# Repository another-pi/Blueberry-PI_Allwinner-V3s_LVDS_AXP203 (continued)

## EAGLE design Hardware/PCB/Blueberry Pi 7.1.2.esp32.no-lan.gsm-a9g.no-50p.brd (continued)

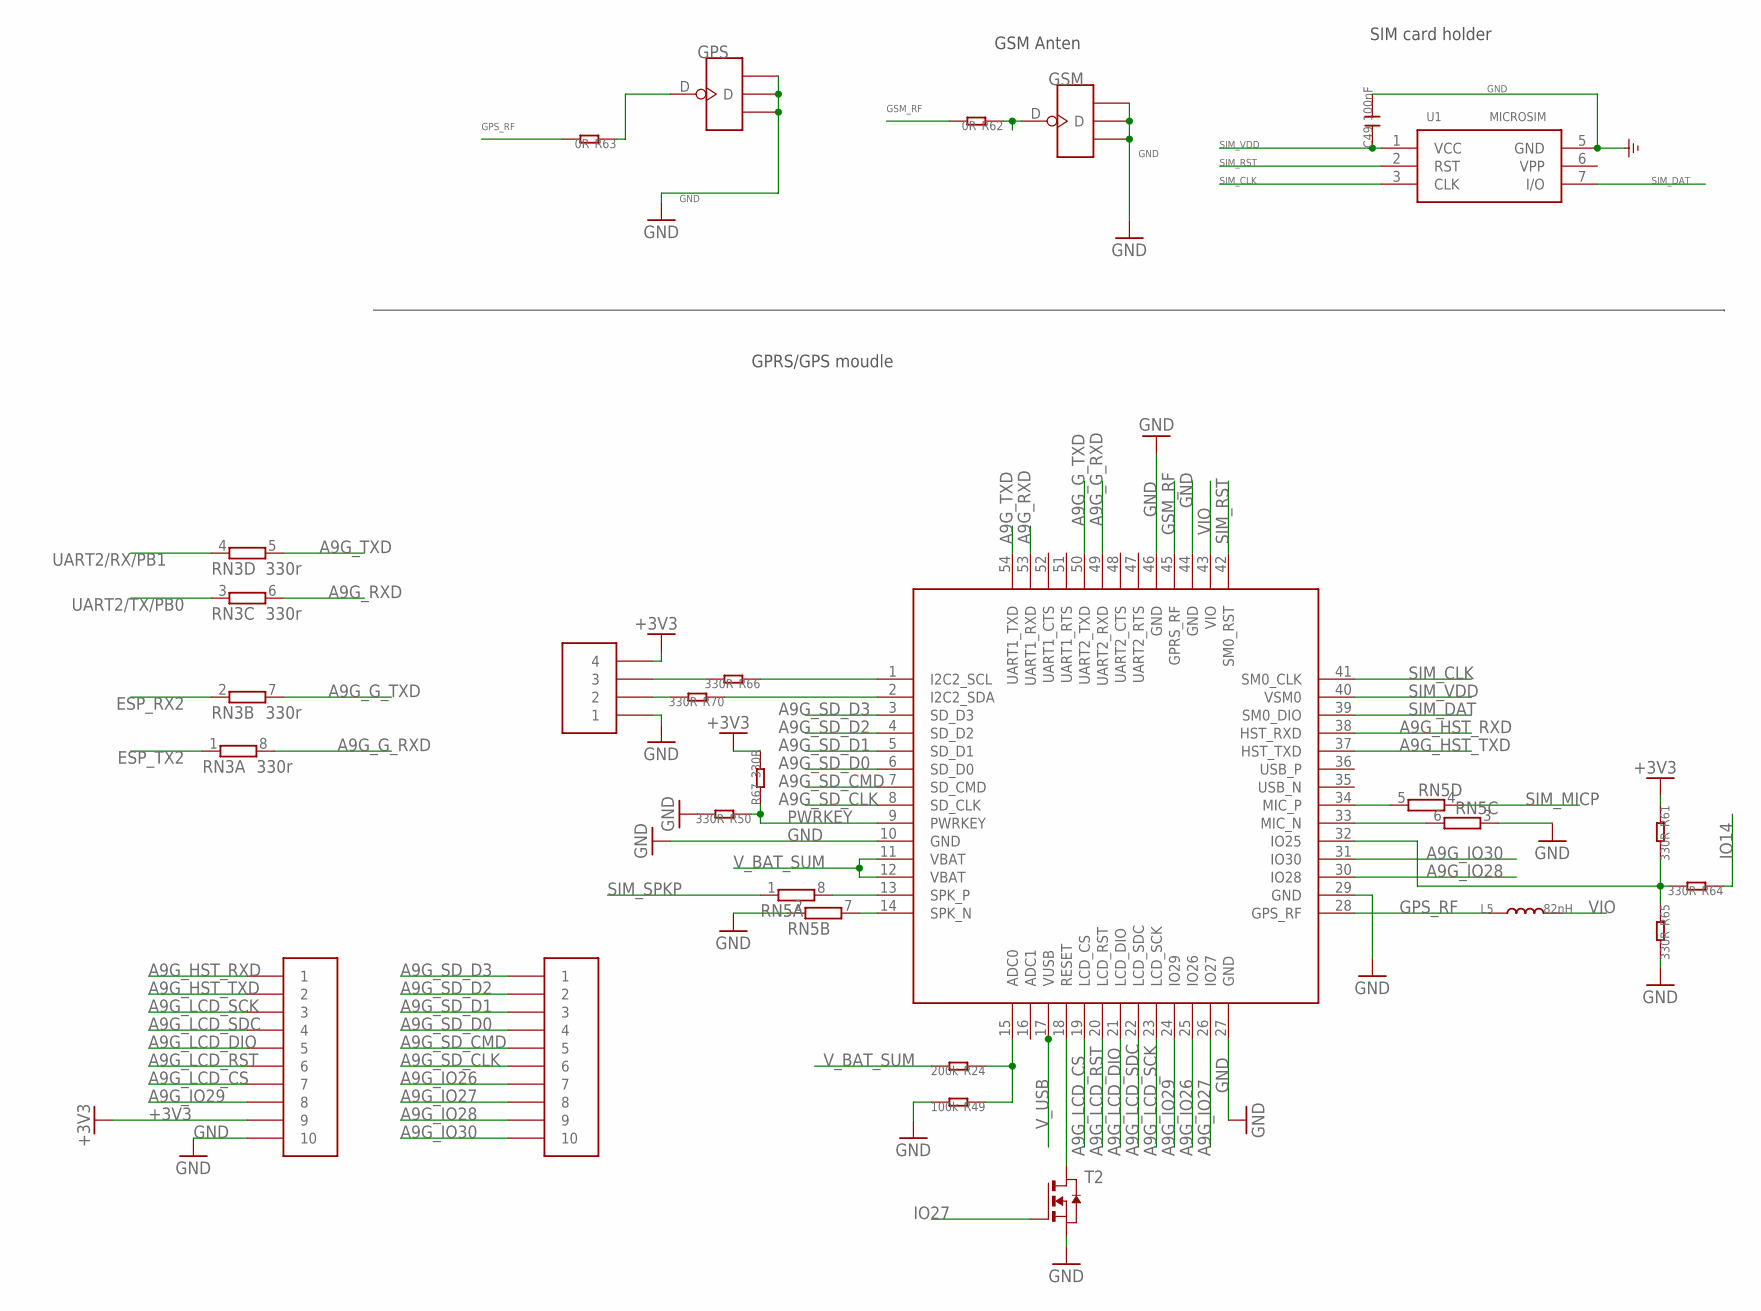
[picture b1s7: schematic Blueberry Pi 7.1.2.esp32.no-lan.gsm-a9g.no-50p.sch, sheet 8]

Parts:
C49: 100nF; C0603
DBG-COM1, DBG-COM2: HDR-1.27MM-110; HDR-1.27MM-1*10
GPS: ANTENNA-U-FL; 4P-U-FL
GSM: ANTENNA-U-FL; 4P-U-FL
L5: 82nH; L0603
R24: 200k; R0603
R49: 100k; R0603
R50, R61, R64, R65, R66, R67, R70: 330R; R0603
R62, R63: 0R; R0603
RN3: 330r; EXB38V
RN5: 4R-NEXB38V; EXB38V
T2: NMOSSOT23; SOT-23
U1: MICROSIM
U6: A9G
U$20: HDR-1.27MM-14; HDR-1.27MM-1*4

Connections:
+3V3: DBG-COM1.P$9 (9), R61.1, R67.2, U$20.P$4 (4); also elsewhere on the board
A9G_G_RXD: RN3.8 (2), U6.49 (UART2_RXD)
A9G_G_TXD: RN3.7 (2), U6.50 (UART2_TXD)
A9G_HST_RXD: DBG-COM1.P$1 (1), U6.38 (HST_RXD)
A9G_HST_TXD: DBG-COM1.P$2 (2), U6.37 (HST_TXD)
A9G_IO26: DBG-COM2.P$7 (7), U6.25 (IO26)
A9G_IO27: DBG-COM2.P$8 (8), U6.26 (IO27)
A9G_IO28: DBG-COM2.P$9 (9), U6.30 (IO28)
A9G_IO29: DBG-COM1.P$8 (8), U6.24 (IO29)
A9G_IO30: DBG-COM2.P$10 (10), U6.31 (IO30)
A9G_LCD_CS: DBG-COM1.P$7 (7), U6.19 (LCD_CS)
A9G_LCD_DIO: DBG-COM1.P$5 (5), U6.21 (LCD_DIO)
A9G_LCD_RST: DBG-COM1.P$6 (6), U6.20 (LCD_RST)
A9G_LCD_SCK: DBG-COM1.P$3 (3), U6.23 (LCD_SCK)
A9G_LCD_SDC: DBG-COM1.P$4 (4), U6.22 (LCD_SDC)
A9G_RXD: RN3.6 (2), U6.53 (UART1_RXD)
A9G_SD_CLK: DBG-COM2.P$6 (6), U6.8 (SD_CLK)
A9G_SD_CMD: DBG-COM2.P$5 (5), U6.7 (SD_CMD)
A9G_SD_D0: DBG-COM2.P$4 (4), U6.6 (SD_D0)
A9G_SD_D1: DBG-COM2.P$3 (3), U6.5 (SD_D1)
A9G_SD_D2: DBG-COM2.P$2 (2), U6.4 (SD_D2)
A9G_SD_D3: DBG-COM2.P$1 (1), U6.3 (SD_D3)
A9G_TXD: RN3.5 (2), U6.54 (UART1_TXD)
ESP_RX2: RN3.2 (1); also elsewhere on the board
ESP_TX2: RN3.1; also elsewhere on the board
GND: C49.2, DBG-COM1.P$10 (10), GPS.GND1, GPS.GND2, GPS.GND3, GSM.GND1, GSM.GND2, GSM.GND3, R49.2, R50.2, R65.2, RN5.2 (1), RN5.3 (1), T2.2 (S), U1.5 (GND), U6.10 (GND), U6.27 (GND), U6.29 (GND), U6.44 (GND), U6.46 (GND), U$20.P$1 (1); also elsewhere on the board
GPS_RF: L5.1, R63.2, U6.28 (GPS_RF)
GSM_RF: R62.2, U6.45 (GPRS_RF)
IO14: R64.1; also elsewhere on the board
IO27: T2.3 (G); also elsewhere on the board
unnamed: R24.1, R49.1, U6.15 (ADC0)
unnamed: RN5.6 (2), U6.33 (MIC_N)
unnamed: RN5.7 (2), U6.14 (SPK_N)
unnamed: R61.2, R64.2, R65.1, U6.32 (IO25)
unnamed: T2.1 (D), U6.18 (RESET)
unnamed: RN5.8 (2), U6.13 (SPK_P)
unnamed: R66.1, U6.1 (I2C2_SCL)
unnamed: GSM.D, R62.1
unnamed: GPS.D, R63.1
unnamed: R70.2, U$20.P$2 (2)
unnamed: R70.1, U6.2 (I2C2_SDA)
unnamed: RN5.5 (2), U6.34 (MIC_P)
unnamed: R66.2, U$20.P$3 (3)
PWRKEY: R50.1, R67.1, U6.9 (PWRKEY)
SIM_CLK: U1.3 (CLK), U6.41 (SM0_CLK)
SIM_DAT: U1.7 (I/O), U6.39 (SM0_DIO)
SIM_MICP: RN5.4 (1); also elsewhere on the board
SIM_RST: U1.2 (RST), U6.42 (SM0_RST)
SIM_SPKP: RN5.1; also elsewhere on the board
SIM_VDD: C49.1, U1.1 (VCC), U6.40 (VSM0)
UART2/RX/PB1: RN3.4 (1); also elsewhere on the board
UART2/TX/PB0: RN3.3 (1); also elsewhere on the board
VIO: L5.2, U6.43 (VIO)
V_BAT_SUM: R24.2, U6.11 (VBAT), U6.12 (VBAT); also elsewhere on the board
V_USB: U6.17 (VUSB); also elsewhere on the board

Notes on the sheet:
SIM card holder
GSM Anten
GPRS/GPS moudle

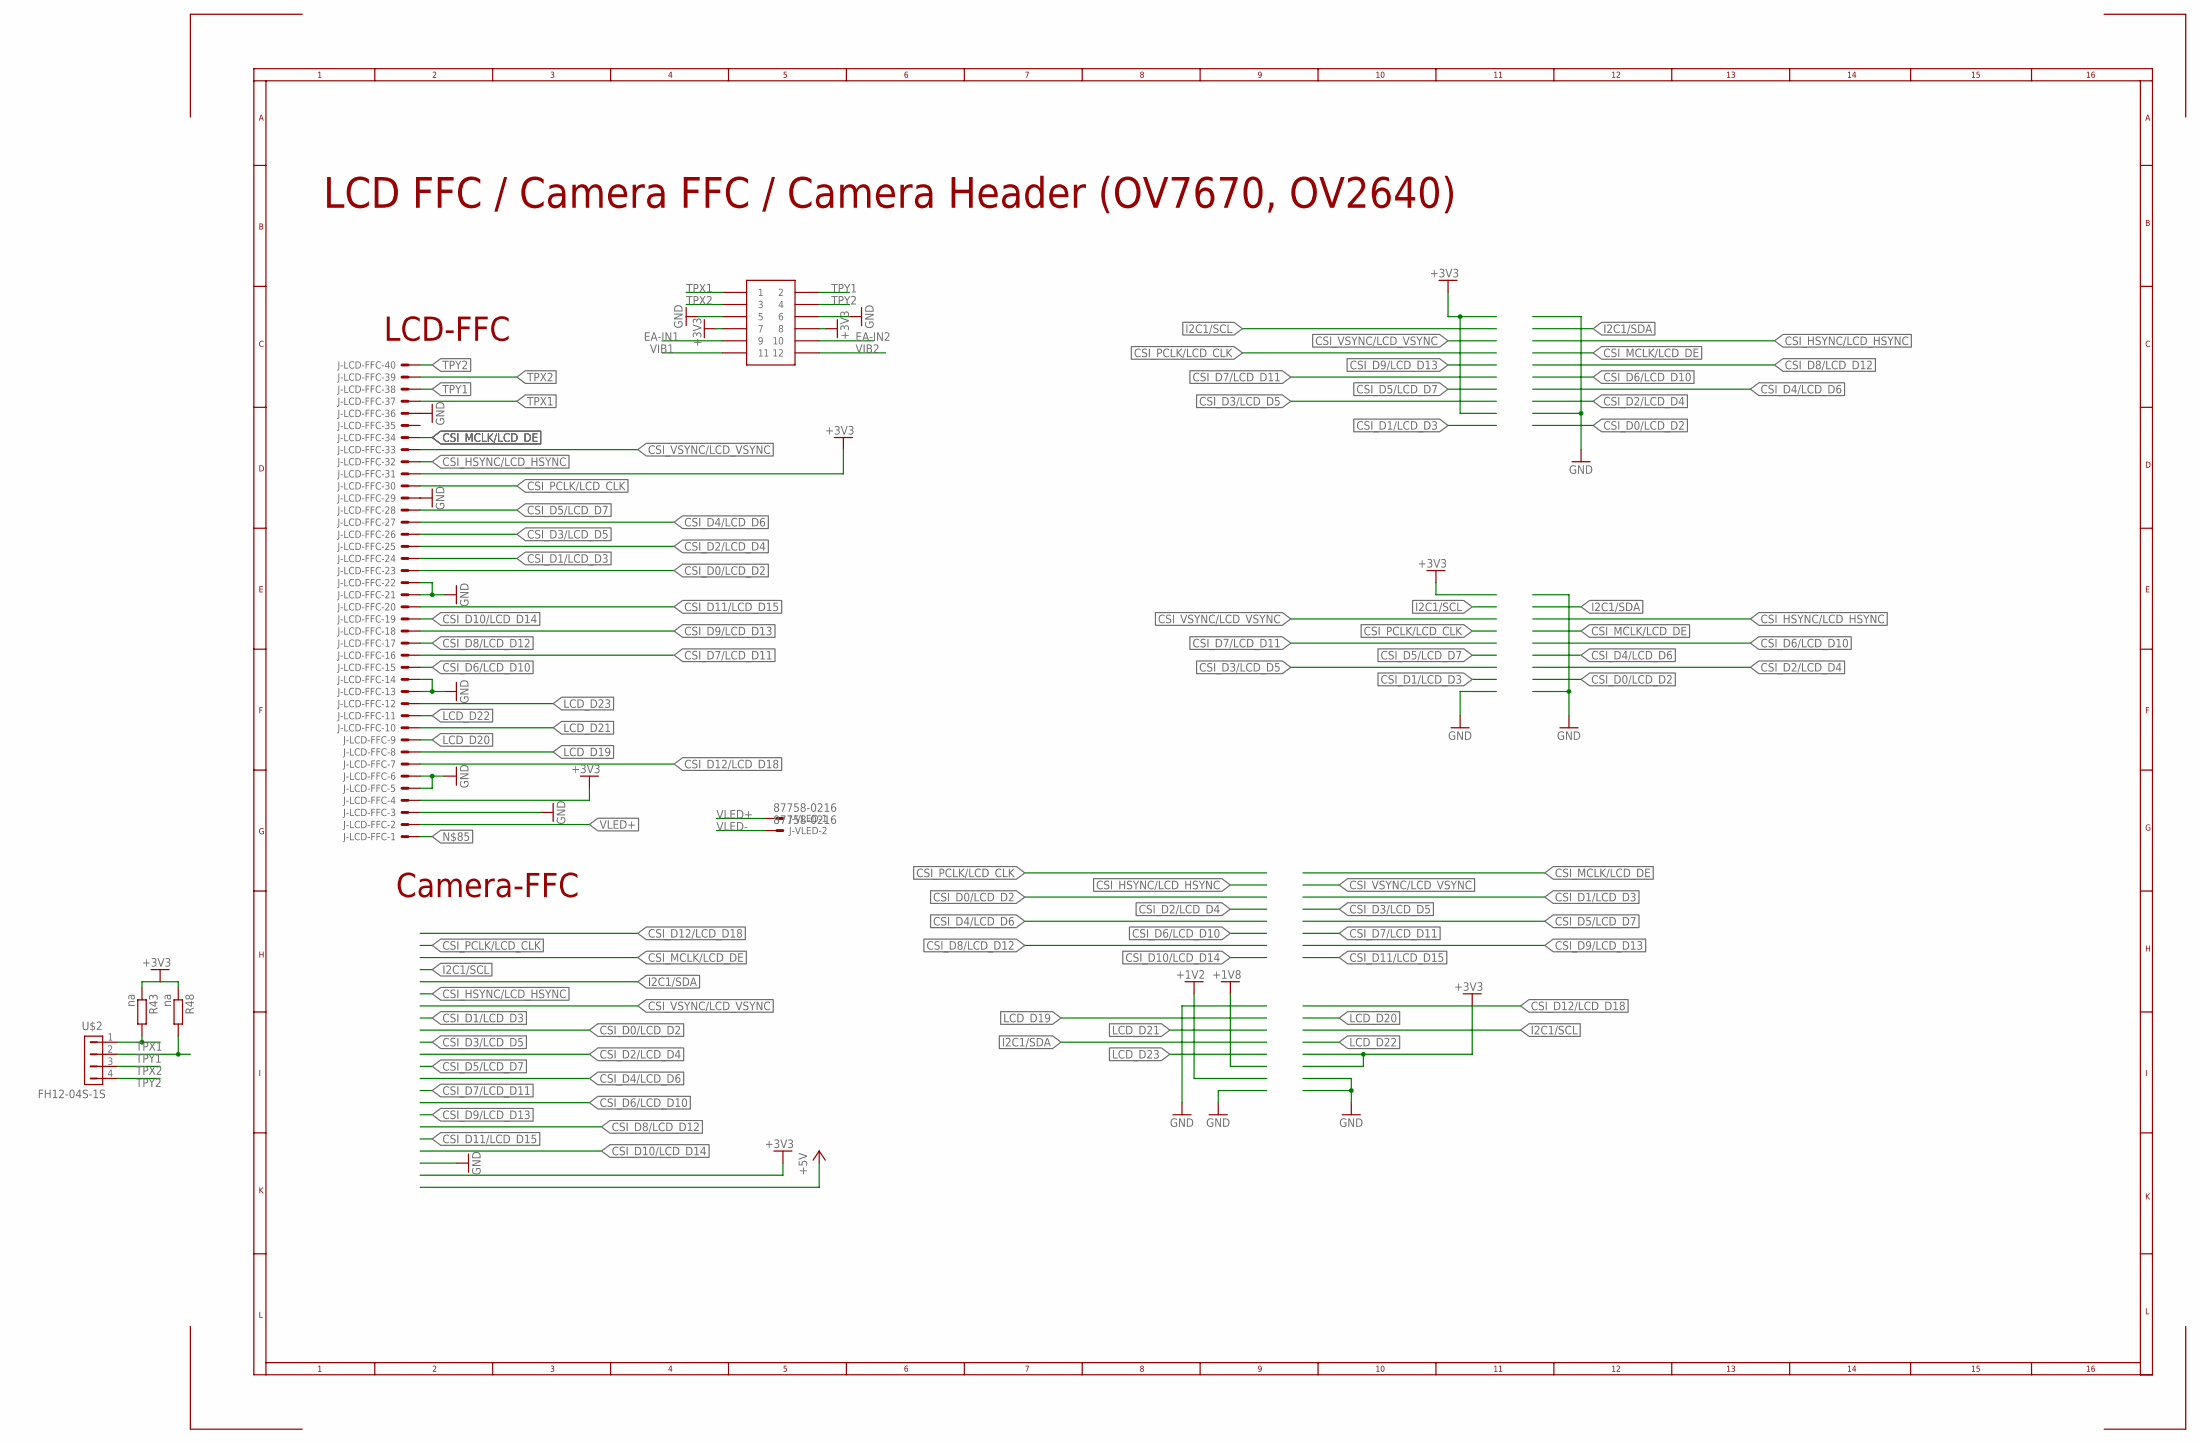
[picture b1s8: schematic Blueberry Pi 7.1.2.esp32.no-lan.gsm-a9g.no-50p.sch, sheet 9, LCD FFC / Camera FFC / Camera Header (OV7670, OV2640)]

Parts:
J-LCD-FFC: 40PINFPCH15-1LW; XF2H-4015-1LW
J-VLED: 87758-0216
R43, R48: na; R0603
U$2: FH12-04S-1S; FH12-04S-1SH
U$18: HDR-1.27MM-62; HDR-1.27MM-6*2

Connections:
+3V3: J-LCD-FFC.4 (MS), J-LCD-FFC.31 (MS), R43.1, R48.1, U$18.P$7 (7), U$18.P$8 (8); also elsewhere on the board
CSI_D0/LCD_D2: J-LCD-FFC.23 (MS); also elsewhere on the board
CSI_D1/LCD_D3: J-LCD-FFC.24 (MS); also elsewhere on the board
CSI_D2/LCD_D4: J-LCD-FFC.25 (MS); also elsewhere on the board
CSI_D3/LCD_D5: J-LCD-FFC.26 (MS); also elsewhere on the board
CSI_D4/LCD_D6: J-LCD-FFC.27 (MS); also elsewhere on the board
CSI_D5/LCD_D7: J-LCD-FFC.28 (MS); also elsewhere on the board
CSI_D6/LCD_D10: J-LCD-FFC.15 (MS); also elsewhere on the board
CSI_D7/LCD_D11: J-LCD-FFC.16 (MS); also elsewhere on the board
CSI_D8/LCD_D12: J-LCD-FFC.17 (MS); also elsewhere on the board
CSI_D9/LCD_D13: J-LCD-FFC.18 (MS); also elsewhere on the board
CSI_D10/LCD_D14: J-LCD-FFC.19 (MS); also elsewhere on the board
CSI_D11/LCD_D15: J-LCD-FFC.20 (MS); also elsewhere on the board
CSI_D12/LCD_D18: J-LCD-FFC.7 (MS); also elsewhere on the board
CSI_HSYNC/LCD_HSYNC: J-LCD-FFC.32 (MS); also elsewhere on the board
CSI_MCLK/LCD_DE: J-LCD-FFC.34 (MS); also elsewhere on the board
CSI_PCLK/LCD_CLK: J-LCD-FFC.30 (MS); also elsewhere on the board
CSI_VSYNC/LCD_VSYNC: J-LCD-FFC.33 (MS); also elsewhere on the board
EA-IN1: U$18.P$9 (9); also elsewhere on the board
EA-IN2: U$18.P$10 (10); also elsewhere on the board
GND: J-LCD-FFC.3 (MS), J-LCD-FFC.5 (MS), J-LCD-FFC.6 (MS), J-LCD-FFC.13 (MS), J-LCD-FFC.14 (MS), J-LCD-FFC.21 (MS), J-LCD-FFC.22 (MS), J-LCD-FFC.29 (MS), J-LCD-FFC.36 (MS), U$18.P$5 (5), U$18.P$6 (6); also elsewhere on the board
LCD_D19: J-LCD-FFC.8 (MS); also elsewhere on the board
LCD_D20: J-LCD-FFC.9 (MS); also elsewhere on the board
LCD_D21: J-LCD-FFC.10 (MS); also elsewhere on the board
LCD_D22: J-LCD-FFC.11 (MS); also elsewhere on the board
LCD_D23: J-LCD-FFC.12 (MS); also elsewhere on the board
TPX1: J-LCD-FFC.37 (MS), R43.2, U$2.1, U$18.P$1 (1); also elsewhere on the board
TPX2: J-LCD-FFC.39 (MS), U$2.3, U$18.P$3 (3); also elsewhere on the board
TPY1: J-LCD-FFC.38 (MS), R48.2, U$2.2, U$18.P$2 (2); also elsewhere on the board
TPY2: J-LCD-FFC.40 (MS), U$2.4, U$18.P$4 (4); also elsewhere on the board
VIB1: U$18.P$11 (11); also elsewhere on the board
VIB2: U$18.P$12 (12); also elsewhere on the board
VLED+: J-LCD-FFC.2 (MS), J-VLED.1; also elsewhere on the board
VLED-: J-VLED.2; also elsewhere on the board

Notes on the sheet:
LCD-FFC
Camera-FFC
LCD FFC / Camera FFC / Camera Header (OV7670, OV2640)

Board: 2 copper layers, 202 parts (107 on the bottom side), 204 nets, no tracks yet.

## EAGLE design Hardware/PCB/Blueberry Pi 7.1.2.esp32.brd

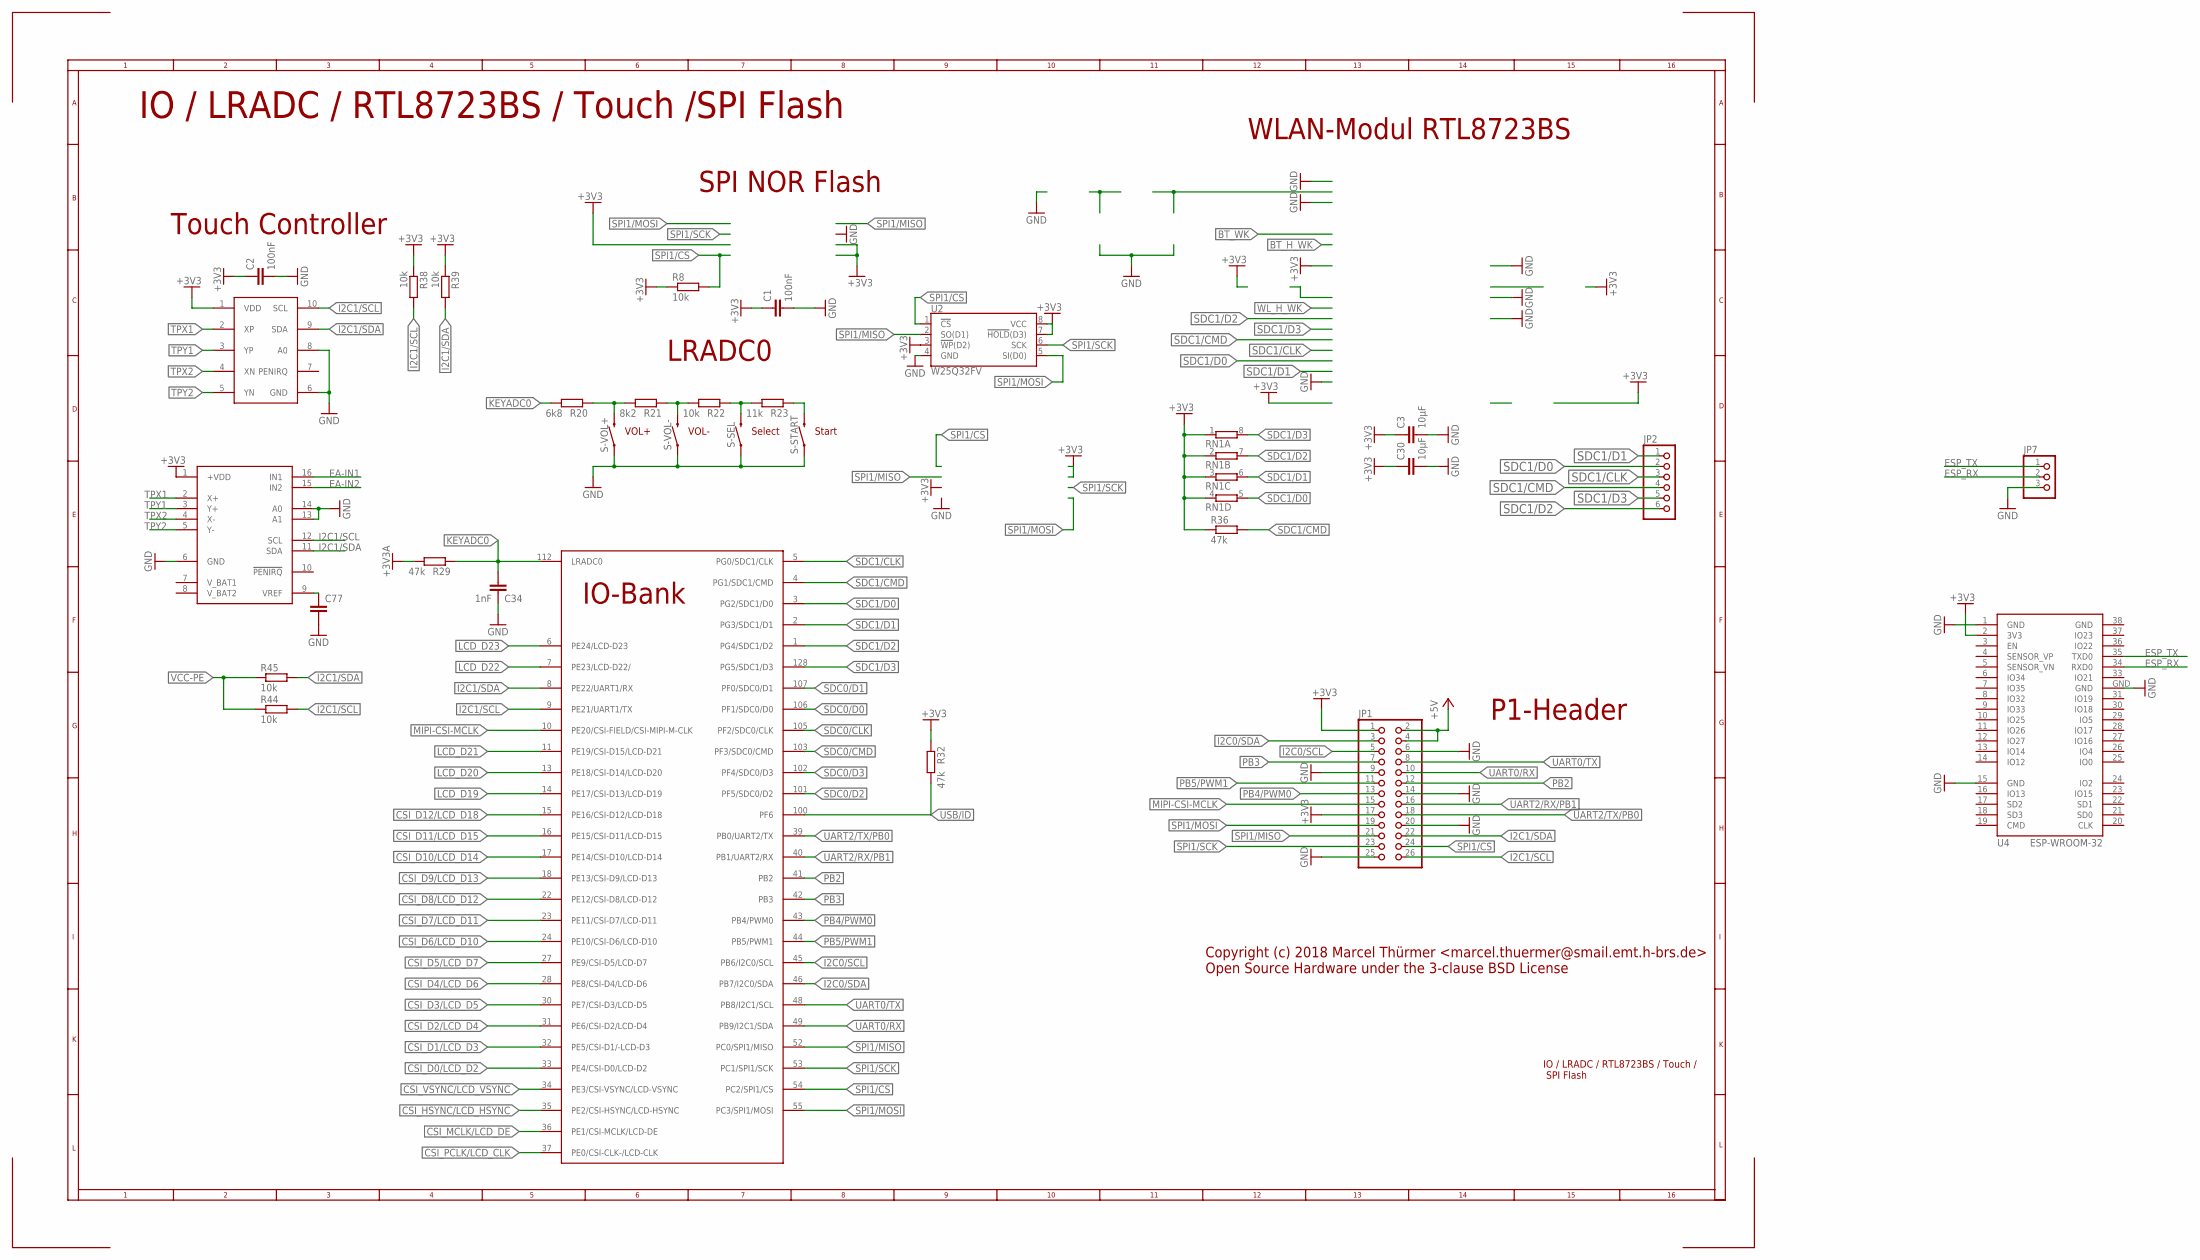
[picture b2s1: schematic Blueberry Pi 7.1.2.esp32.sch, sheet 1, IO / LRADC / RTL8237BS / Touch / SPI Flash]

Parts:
C1, C2: 100nF; C0603
C3, C30: 10µF; C0805
C34: 1nF; C0603
C77: C-EUC0805; C0805
JP1: PINHD-2X13; 2X13
JP2: PINHD-1X6_2.00; 1X06M
JP7: PINHD-1X3M; 1X03M
R8, R22, R38, R39, R44, R45: 10k; R0603
R20: 6k8; R0603
R21: 8k2; R0603
R23: 11k; R0603
R29, R32, R36: 47k; R0603
RN1: 4R-NEXB38V; EXB38V
S-SEL: SPARKFUN-SWITCHES_MOMENTARY-SWITCH-SPST-SMD-5.2-R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; SPARKFUN-SWITCHES_TACTILE_SWITCH_SMD_5.2MM
S-START: SPARKFUN-SWITCHES_MOMENTARY-SWITCH-SPST-SMD-5.2-R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; SPARKFUN-SWITCHES_TACTILE_SWITCH_SMD_5.2MM
S-VOL+: SPARKFUN-SWITCHES_MOMENTARY-SWITCH-SPST-SMD-5.2-R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; SPARKFUN-SWITCHES_TACTILE_SWITCH_SMD_5.2MM
S-VOL-: SPARKFUN-SWITCHES_MOMENTARY-SWITCH-SPST-SMD-5.2-R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; SPARKFUN-SWITCHES_TACTILE_SWITCH_SMD_5.2MM
U2: W25Q32FV; SOIC-8
U4: ESP-WROOM-32
U$1: V3S; QFP-128
U$7: TSC2003; TSSOP16
U$8: NS2009; MSOP10

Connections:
+3V3: C1.1, C2.1, C3.1, C30.1, JP1.1, JP1.17, R8.1, R32.1, R36.1, R38.1, R39.1, RN1.1, RN1.2 (1), RN1.3 (1), RN1.4 (1), U2.3 (!WP!(D2)), U2.7 (!HOLD!(D3)), U2.8 (VCC), U4.2 (3V3), U$7.1 (+VDD), U$8.1 (VDD); also elsewhere on the board
+3V3A: R29.2; also elsewhere on the board
+5V: JP1.2, JP1.4; also elsewhere on the board
CSI_D0/LCD_D2: U$1.33 (PE4/CSI-D0/LCD-D2); also elsewhere on the board
CSI_D1/LCD_D3: U$1.32 (PE5/CSI-D1/-LCD-D3); also elsewhere on the board
CSI_D2/LCD_D4: U$1.31 (PE6/CSI-D2/LCD-D4); also elsewhere on the board
CSI_D3/LCD_D5: U$1.30 (PE7/CSI-D3/LCD-D5); also elsewhere on the board
CSI_D4/LCD_D6: U$1.28 (PE8/CSI-D4/LCD-D6); also elsewhere on the board
CSI_D5/LCD_D7: U$1.27 (PE9/CSI-D5/LCD-D7); also elsewhere on the board
CSI_D6/LCD_D10: U$1.24 (PE10/CSI-D6/LCD-D10); also elsewhere on the board
CSI_D7/LCD_D11: U$1.23 (PE11/CSI-D7/LCD-D11); also elsewhere on the board
CSI_D8/LCD_D12: U$1.22 (PE12/CSI-D8/LCD-D12); also elsewhere on the board
CSI_D9/LCD_D13: U$1.18 (PE13/CSI-D9/LCD-D13); also elsewhere on the board
CSI_D10/LCD_D14: U$1.17 (PE14/CSI-D10/LCD-D14); also elsewhere on the board
CSI_D11/LCD_D15: U$1.16 (PE15/CSI-D11/LCD-D15); also elsewhere on the board
CSI_D12/LCD_D18: U$1.15 (PE16/CSI-D12/LCD-D18); also elsewhere on the board
CSI_HSYNC/LCD_HSYNC: U$1.35 (PE2/CSI-HSYNC/LCD-HSYNC); also elsewhere on the board
CSI_MCLK/LCD_DE: U$1.36 (PE1/CSI-MCLK/LCD-DE); also elsewhere on the board
CSI_PCLK/LCD_CLK: U$1.37 (PE0/CSI-CLK-/LCD-CLK); also elsewhere on the board
CSI_VSYNC/LCD_VSYNC: U$1.34 (PE3/CSI-VSYNC/LCD-VSYNC); also elsewhere on the board
EA-IN1: U$7.16 (IN1); also elsewhere on the board
EA-IN2: U$7.15 (IN2); also elsewhere on the board
ESP_RX: JP7.2, U4.34 (RXD0)
ESP_TX: JP7.1, U4.35 (TXD0)
GND: C1.2, C2.2, C3.2, C30.2, C34.1, C77.2, JP1.6, JP1.9, JP1.14, JP1.20, JP1.25, JP7.3, S-SEL.1, S-SEL.2 (1), S-START.1, S-START.2 (1), S-VOL+.1, S-VOL+.2 (1), S-VOL-.1, S-VOL-.2 (1), U2.4 (GND), U4.1 (GND), U4.15 (GND), U4.38 (GND), U4.GND, U$7.6 (GND), U$7.13 (A1), U$7.14 (A0), U$8.6 (GND), U$8.8 (A0); also elsewhere on the board
I2C0/SCL: JP1.5, U$1.45 (PB6/I2C0/SCL)
I2C0/SDA: JP1.3, U$1.46 (PB7/I2C0/SDA)
I2C1/SCL: JP1.26, R38.2, R44.2, U$1.9 (PE21/UART1/TX), U$7.12 (SCL), U$8.10 (SCL); also elsewhere on the board
I2C1/SDA: JP1.22, R39.2, R45.2, U$1.8 (PE22/UART1/RX), U$7.11 (SDA), U$8.9 (SDA); also elsewhere on the board
KEYADC0: C34.2, R20.2, R29.1, U$1.112 (LRADC0)
LCD_D19: U$1.14 (PE17/CSI-D13/LCD-D19); also elsewhere on the board
LCD_D20: U$1.13 (PE18/CSI-D14/LCD-D20); also elsewhere on the board
LCD_D21: U$1.11 (PE19/CSI-D15/LCD-D21); also elsewhere on the board
LCD_D22: U$1.7 (PE23/LCD-D22/); also elsewhere on the board
LCD_D23: U$1.6 (PE24/LCD-D23); also elsewhere on the board
MIPI-CSI-MCLK: JP1.15, U$1.10 (PE20/CSI-FIELD/CSI-MIPI-M-CLK); also elsewhere on the board
unnamed: R20.1, R21.2, S-VOL+.3 (2), S-VOL+.4 (2)
unnamed: C77.1, U$7.9 (VREF)
unnamed: R21.1, R22.2, S-VOL-.3 (2), S-VOL-.4 (2)
unnamed: R22.1, R23.2, S-SEL.3 (2), S-SEL.4 (2)
unnamed: R23.1, S-START.3 (2), S-START.4 (2)
PB2: JP1.12, U$1.41 (PB2); also elsewhere on the board
PB3: JP1.7, U$1.42 (PB3); also elsewhere on the board
PB4/PWM0: JP1.13, U$1.43 (PB4/PWM0)
PB5/PWM1: JP1.11, U$1.44 (PB5/PWM1)
SDC0/CLK: U$1.105 (PF2/SDC0/CLK); also elsewhere on the board
SDC0/CMD: U$1.103 (PF3/SDC0/CMD); also elsewhere on the board
SDC0/D0: U$1.106 (PF1/SDC0/D0); also elsewhere on the board
SDC0/D1: U$1.107 (PF0/SDC0/D1); also elsewhere on the board
SDC0/D2: U$1.101 (PF5/SDC0/D2); also elsewhere on the board
SDC0/D3: U$1.102 (PF4/SDC0/D3); also elsewhere on the board
SDC1/CLK: JP2.3, U$1.5 (PG0/SDC1/CLK)
SDC1/CMD: JP2.4, R36.2, U$1.4 (PG1/SDC1/CMD)
SDC1/D0: JP2.2, RN1.5 (2), U$1.3 (PG2/SDC1/D0)
SDC1/D1: JP2.1, RN1.6 (2), U$1.2 (PG3/SDC1/D1)
SDC1/D2: JP2.6, RN1.7 (2), U$1.1 (PG4/SDC1/D2)
SDC1/D3: JP2.5, RN1.8 (2), U$1.128 (PG5/SDC1/D3)
SPI1/CS: JP1.24, R8.2, U2.1 (!CS!), U$1.54 (PC2/SPI1/CS)
SPI1/MISO: JP1.21, U2.2 (SO(D1)), U$1.52 (PC0/SPI1/MISO)
SPI1/MOSI: JP1.19, U2.5 (SI(D0)), U$1.55 (PC3/SPI1/MOSI)
SPI1/SCK: JP1.23, U2.6 (SCK), U$1.53 (PC1/SPI1/SCK)
TPX1: U$7.2 (X+), U$8.2 (XP); also elsewhere on the board
TPX2: U$7.4 (X-), U$8.4 (XN); also elsewhere on the board
TPY1: U$7.3 (Y+), U$8.3 (YP); also elsewhere on the board
TPY2: U$7.5 (Y-), U$8.5 (YN); also elsewhere on the board
UART0/RX: JP1.10, U$1.49 (PB9/I2C1/SDA)
UART0/TX: JP1.8, U$1.48 (PB8/I2C1/SCL)
UART2/RX/PB1: JP1.16, U$1.40 (PB1/UART2/RX)
UART2/TX/PB0: JP1.18, U$1.39 (PB0/UART2/TX)
USB/ID: R32.2, U$1.100 (PF6); also elsewhere on the board
VCC-PE: R44.1, R45.1

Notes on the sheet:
IO / LRADC / RTL8723BS / Touch / SPI Flash
Copyright (c) 2018 Marcel Thürmer <marcel.thuermer@smail.emt.h-brs.de> Open Source Hardware under the 3-clause BSD License
SPI NOR Flash
WLAN-Modul RTL8723BS
P1-Header
LRADC0
Start
Select
VOL-
VOL+
Touch Controller
IO / LRADC / RTL8723BS / Touch /SPI Flash

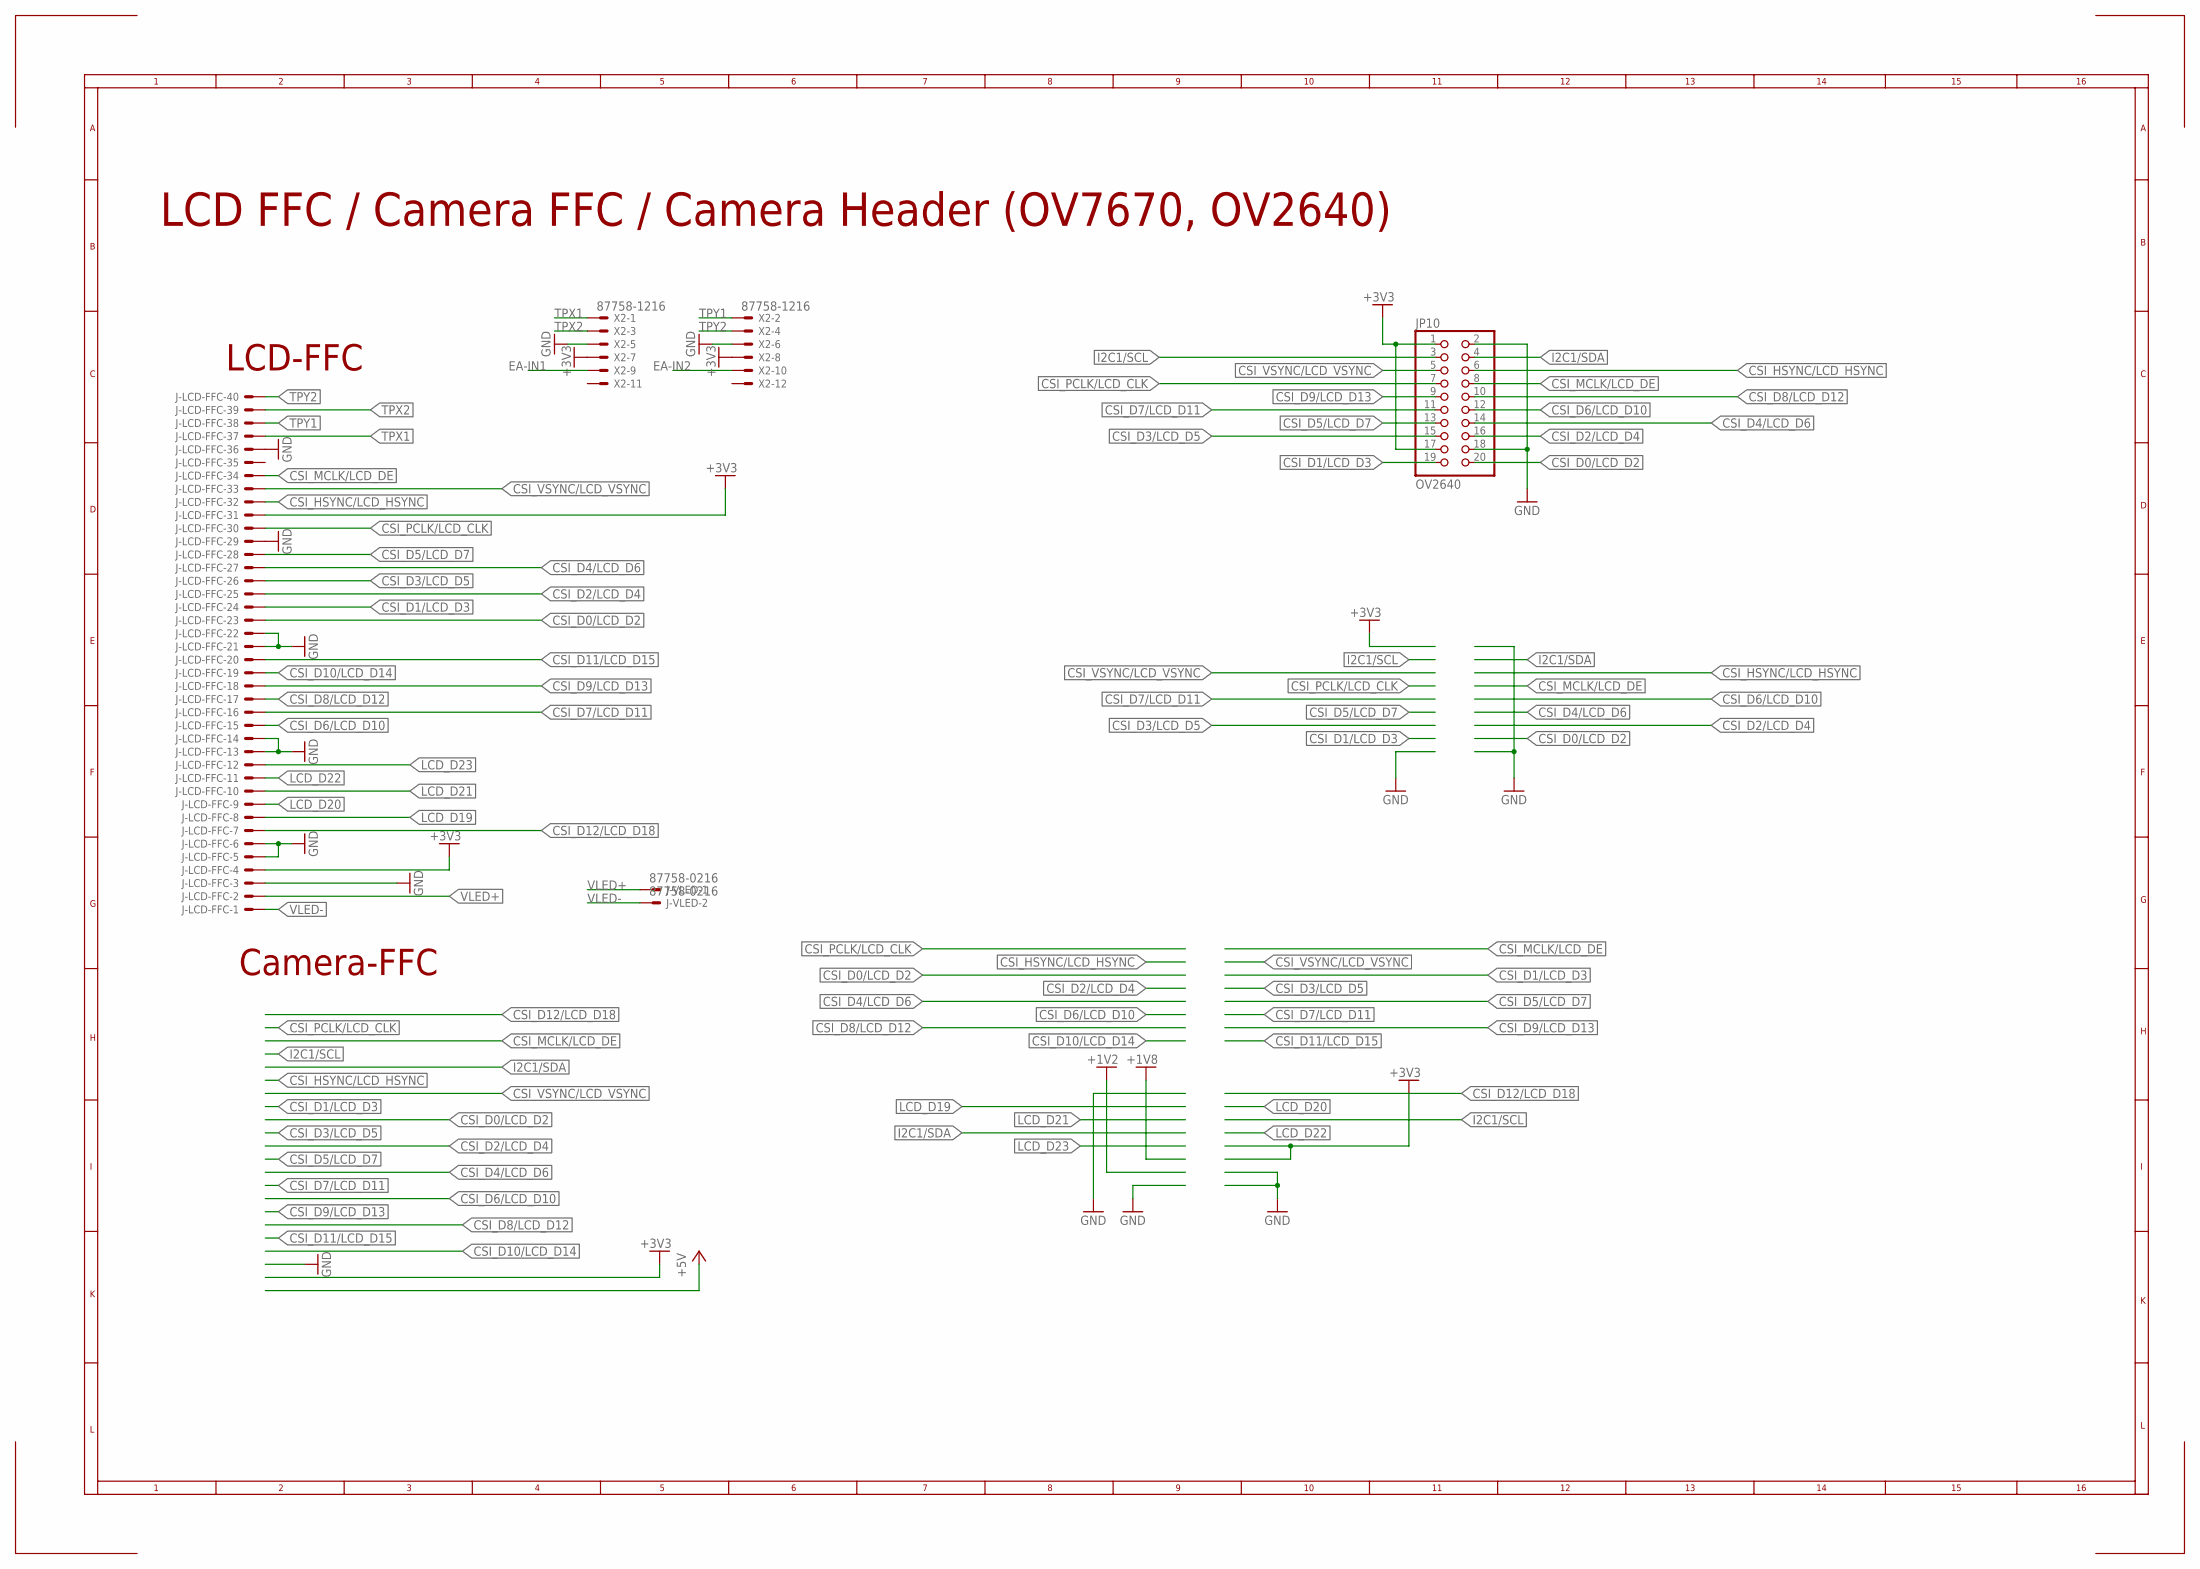
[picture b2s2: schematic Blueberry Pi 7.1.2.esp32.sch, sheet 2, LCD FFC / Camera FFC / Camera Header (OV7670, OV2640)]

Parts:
J-LCD-FFC: 40PINFPCH15-1LW; XF2H-4015-1LW
J-VLED: 87758-0216
JP10: OV2640; 2X10
X2: 87758-1216

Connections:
+3V3: J-LCD-FFC.4 (MS), J-LCD-FFC.31 (MS), JP10.1, JP10.17, X2.7, X2.8; also elsewhere on the board
CSI_D0/LCD_D2: J-LCD-FFC.23 (MS), JP10.20; also elsewhere on the board
CSI_D1/LCD_D3: J-LCD-FFC.24 (MS), JP10.19; also elsewhere on the board
CSI_D2/LCD_D4: J-LCD-FFC.25 (MS), JP10.16; also elsewhere on the board
CSI_D3/LCD_D5: J-LCD-FFC.26 (MS), JP10.15; also elsewhere on the board
CSI_D4/LCD_D6: J-LCD-FFC.27 (MS), JP10.14; also elsewhere on the board
CSI_D5/LCD_D7: J-LCD-FFC.28 (MS), JP10.13; also elsewhere on the board
CSI_D6/LCD_D10: J-LCD-FFC.15 (MS), JP10.12; also elsewhere on the board
CSI_D7/LCD_D11: J-LCD-FFC.16 (MS), JP10.11; also elsewhere on the board
CSI_D8/LCD_D12: J-LCD-FFC.17 (MS), JP10.10; also elsewhere on the board
CSI_D9/LCD_D13: J-LCD-FFC.18 (MS), JP10.9; also elsewhere on the board
CSI_D10/LCD_D14: J-LCD-FFC.19 (MS); also elsewhere on the board
CSI_D11/LCD_D15: J-LCD-FFC.20 (MS); also elsewhere on the board
CSI_D12/LCD_D18: J-LCD-FFC.7 (MS); also elsewhere on the board
CSI_HSYNC/LCD_HSYNC: J-LCD-FFC.32 (MS), JP10.6; also elsewhere on the board
CSI_MCLK/LCD_DE: J-LCD-FFC.34 (MS), JP10.8; also elsewhere on the board
CSI_PCLK/LCD_CLK: J-LCD-FFC.30 (MS), JP10.7; also elsewhere on the board
CSI_VSYNC/LCD_VSYNC: J-LCD-FFC.33 (MS), JP10.5; also elsewhere on the board
EA-IN1: X2.9; also elsewhere on the board
EA-IN2: X2.10; also elsewhere on the board
GND: J-LCD-FFC.3 (MS), J-LCD-FFC.5 (MS), J-LCD-FFC.6 (MS), J-LCD-FFC.13 (MS), J-LCD-FFC.14 (MS), J-LCD-FFC.21 (MS), J-LCD-FFC.22 (MS), J-LCD-FFC.29 (MS), J-LCD-FFC.36 (MS), JP10.2, JP10.18, X2.5, X2.6; also elsewhere on the board
I2C1/SCL: JP10.3; also elsewhere on the board
I2C1/SDA: JP10.4; also elsewhere on the board
LCD_D19: J-LCD-FFC.8 (MS); also elsewhere on the board
LCD_D20: J-LCD-FFC.9 (MS); also elsewhere on the board
LCD_D21: J-LCD-FFC.10 (MS); also elsewhere on the board
LCD_D22: J-LCD-FFC.11 (MS); also elsewhere on the board
LCD_D23: J-LCD-FFC.12 (MS); also elsewhere on the board
TPX1: J-LCD-FFC.37 (MS), X2.1; also elsewhere on the board
TPX2: J-LCD-FFC.39 (MS), X2.3; also elsewhere on the board
TPY1: J-LCD-FFC.38 (MS), X2.2; also elsewhere on the board
TPY2: J-LCD-FFC.40 (MS), X2.4; also elsewhere on the board
VLED+: J-LCD-FFC.2 (MS), J-VLED.1; also elsewhere on the board
VLED-: J-LCD-FFC.1 (MSV), J-VLED.2; also elsewhere on the board

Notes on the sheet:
LCD-FFC
Camera-FFC
LCD FFC / Camera FFC / Camera Header (OV7670, OV2640)
